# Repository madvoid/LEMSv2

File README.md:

# LEMSv2
This is the repository for the second version of the LEMS Sensor Stations. Stay tuned, information will be added as it is generated. A majority of the documentation will be added to this file. Long-term future development will happen at https://github.com/UtahEFD/LEMSv2.

### General TODO

1. Check validity of filenames with more than 8 characters
2. Decagon, the manufacturer of the 5TM soil sensors, has changed their name to Meter, and the 5TM is now called the ECH20 5TM. The DS2 is now called the Atmos 22. The documentation will need to be changed and will probably be done slowly.
3. Major Change: Change the code to read parameters from a text file on the SD card. See if possible to read code from SD card.
4. Delete or separate "File List" from README? Makes it clunky, hard to keep updated. Goal is for files to self explanatory 
5. Update DS2 code to use EnviroDIY's SDI12 library instead of custom library

### PCB TODO
1. Change the parts in the eagle files for BOM lines 11, 29, 30. These parts were out of stock and were replaced by different parts during manufacturing.

### File List
* Code/
  * `Code Instructions.md` - Instructions for uploading
  * LEMSv2/
    * `LEMSv2.ino` - LEMS Arduino Code
    * `DS3231_Alarm1.h` - Header file for corresponding `.cpp` file
    * `DS3231_Alarm1.cpp` - File used to set DS3231 Alarm 1. Developed in test code then copied to this folder
    * `d5TM.h` - Header file for corresponding `.cpp` file
    * `d5TM.cpp` - Library used to interact with 5TM. Developed in test code then copied to this folder
  * Test Code/
    * ADS1115_Test/
      * `ADS1115_Test.ino` - Test code for ADS1115 ADC
    * DS3231_Test/
      * `DS3231_Test.ino` - Test code for DS3231 RTC. Test DS3231 alarm 1
      * `DS3231_Alarm1.h` - Header file for corresponding `.cpp` file
      * `DS3231_Alarm1.c` - Library used to set DS3231 Alarm 1. Developed in here then copied to main code folder
    * DS2_Test/
      * `DS2_Test.ino` - Test code for DS2 anemometer
      * `DS2.h` - Header file for corresponding `.cpp` file
      * `DS2.cpp` - Library used to interact with DS2. Developed here then copied to main code folder
      * `LICENSE` - License to be included with the `SDI12_Zero` library
      * `LICENSE-examples.md` - License to be included with the `SDI12_Zero` library
      * `SDI12_Zero.h` - Header file for corresponding `.cpp` file
      * `SDI12_Zero.cpp` - Library used by DS2 library to interact with DS2. Implements the SDI12 protocal for Arduino Zero.
    * Li200_Test/
      * `Li200_Test.ino` - Test Li200 with intermediate values in calculations printed
    * Teros21_Test/
      * `Teros21_Test.ino` - Test Teros21 and library.
    * Test_5TM/
      * `Test_5TM.ino` - Test code for 5TM Library. 5TM has been working since LEMSv1 but is now made into a library.
      * `d5TM.h` - Header file for corresponding `.cpp` file
      * `d5TM.cpp` - Library used to interact with 5TM. Developed here then copied to main code folder
  * Time_Set/
    * `Time_Set.ino` - Code used to set the time on the DS3231 real time clock
* Data Manipulation/
  * `LemsPlot.m` - View LEMSv2 data plots. Not perfectly adaptable to any file, but will work for a fully instrumented station. To work properly, requires the [Intelligent Dynamic Date Ticks](https://www.mathworks.com/matlabcentral/fileexchange/27075-intelligent-dynamic-date-ticks) file from MathWorks. Can work without it though by commenting out the lines that use it.
  * `importfile.m` - Used to import the LEMSv2 data files. Can only be used on data files from fully instrumented LEMS.
* Hardware Information/
  * `Bill of Materials.xlsx` - Complete parts list
  * `Calibration Constants.xlsx` - Calibration constants for various instruments. For now, only contains Li200 constants.
  * Data Sheets/
    * Multiple data sheets for components
  * Li200R Base/
    * Solidworks/
      * Contains Solidworks files for Li200R base
    * STL Files/
      * Contains print ready STL files for Li200R base
    * `Build Instructions.md` - Tools required for making the Li200R base
  * MLX Housing/
    * `MLX Housing Build Instructions` - Build instructions for MLX90615 housing
  * PCB/
    * `LEMSv2 Board.pdf` - PDF of PCB for easy reference
    * `LEMSv2 Schematic.pdf` - PDF of schematic for easy reference
    * `SAMD21 Breakout Board.jpg` - Reference picture for microcontroller board
  * `Pin List.xlsx` - Pin connection list for SAMD21 Dev Breakout Board
  * `Possible Parts.txt` - Potential parts/Manufacturers to add/use in the future
  * Transimpedance Amplifier/
    * `Transimpedance_Amplifier_Calculations.ipynb` - Jupyter notebook containing transimpedance amplifier calculations
  * `Wiring Information.xlsx` - Information about wiring. What connects to what, etc. Work in progress.
* `LICENSE.TXT` - License
* PCB/
  * LEMSv2 PCB/
    * `Centroid_ScreamingCircuits_smd.ulp` - Eagle ULP script to create centroid data for screaming circuits
    * Gerbers/
      * Contains gerbers for board, plus the panelized gerbers supplied by OSH Park. Also contains the centroid file for Screaming Circuits.
    * `LEMSv2.sch` - LEMSv2 shield schematic
    * `LEMSv2.brd` - LEMSv2 shield layout
    * `OSH_DesignRules.dru` - Eagle design rules for OSH Park
    * `OSHPark_2layer_Eagle7.2.cam` - Modified cam job for OSH Park
  * LEMSv2 PCB Library/
    * `LEMSv2.lbr` - Parts used in the LEMSv2 shield
* `Possible Problems.md` - List of potential hardware problems in the LEMS. Prefer to not have duplicate entries, i.e. one line per problem.
* `README.md` - If you read this line you're actually reading the README. Good job!

### Dependencies
Only 3rd party software dependencies are included in this list. Libraries built into the Arduino software or created for the LEMSv2 software isn't included. You will need the most recent version of the [Arduino IDE](https://www.arduino.cc/en/Main/Software) installed.

* [Adafruit RTC Library](https://github.com/adafruit/RTClib)
* [Adafruit SHT31 Library](https://github.com/adafruit/Adafruit_SHT31)
* [Adafruit Sensor Library](https://github.com/adafruit/Adafruit_Sensor)
* [Adafruit BMP280 Library](https://github.com/adafruit/Adafruit_BMP280_Library)
* [Adafruit MLX90614 Library](https://github.com/adafruit/Adafruit-MLX90614-Library)
* [EnviroDIY SDI-12 Library](https://github.com/EnviroDIY/Arduino-SDI-12) 
* [Soligen2010's fork of the Adafruit ADS1x15 Library](https://github.com/soligen2010/Adafruit_ADS1X15). The default Adafruit ADS1x15 library **doesn't** work.
* In addition, the Sparkfun SAMD21 [board definition](https://raw.githubusercontent.com/sparkfun/Arduino_Boards/master/IDE_Board_Manager/package_sparkfun_index.json
  ) needs to be installed into the Arduino IDE. See [here](https://learn.sparkfun.com/tutorials/samd21-minidev-breakout-hookup-guide/setting-up-arduino) for more info.

### Miscellaneous Notes

- ADS1115 single ended resolution calculation information can be found [here](https://e2e.ti.com/support/data_converters/precision_data_converters/f/73/t/489070)
- ADS1115 over range input information can be found [here](https://e2e.ti.com/support/data_converters/precision_data_converters/f/73/p/398187/1407689#1407689) and [here](https://e2e.ti.com/support/data_converters/precision_data_converters/f/73/t/378122)

### Acknowledgements

* Thanks to [Sparkfun](https://www.sparkfun.com) and [Adafruit](https://www.adafruit.com) for Arduino libraries, components, tutorials, and eagle parts. Many designs and eagle components are directly used from them. Also thanks to [OSH Park](www.oshpark.com) and [Screaming Circuits](www.screamingcircuits.com) for the excellent PCBs and assembly. They were instrumental in getting LEMSv2 completed.

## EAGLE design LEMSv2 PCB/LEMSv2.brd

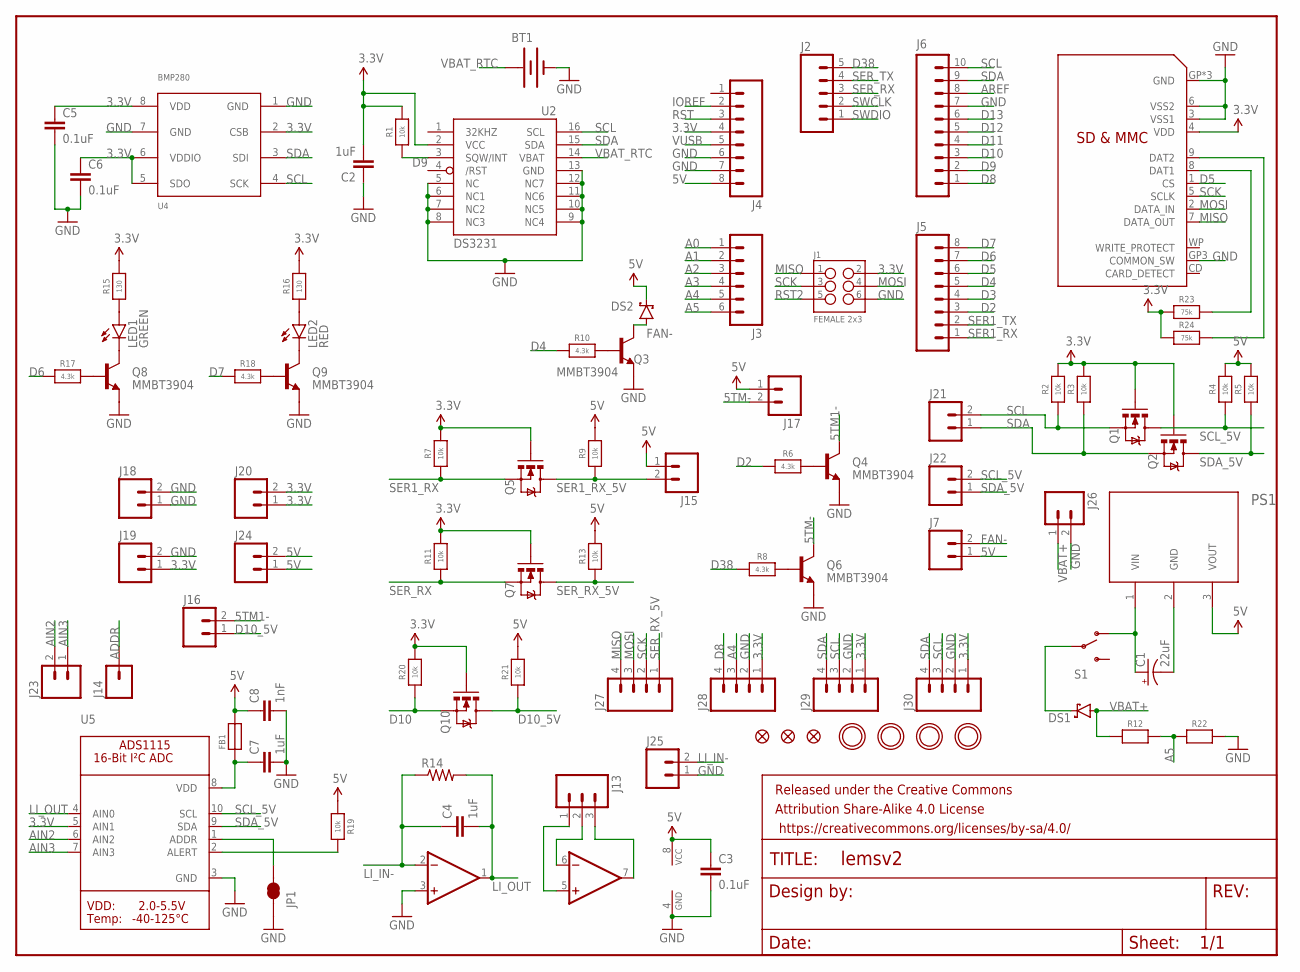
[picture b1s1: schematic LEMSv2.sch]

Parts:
BT1: BATTERY12MM; BATTCON_12MM
C1: 22uF; CPOL-RADIAL-10UF-25V
C2, C4, C7: 1uF; _0805
C3, C5, C6: 0.1uF; _0805
C8: 1nF; _0805
DS1, DS2: DIODE_SCHOTTKY; DO-214AC
FB1: FERRITE; _0805
FID1, FID2, FID3: FIDUCIAL""; FIDUCIAL_1MM
FRAME1: FRAME-LETTERNO_PACKAGE; DUMMY
J1: FEMALE 2x3; 2X3
J2: M05PTH; 1X05
J3: M06SILK_FEMALE_PTH; 1X06
J4, J5: M08; 1X08_ROUND
J6: M10SILK_FEMALE_PTH; 1X10
J7, J15, J16, J17, J18, J19, J20, J21, J22, J23, J24, J25, J26: M023.5MM; SCREWTERMINAL-3.5MM-2
J13: M03PTH; 1X03
J14: M01PTH; 1X01
J27, J28, J29, J30: M04SCREW; SCREWTERMINAL-3.5MM-4
JP1: JUMPER-PAD-2-NC_BY_TRACE; PAD-JUMPER-2-NC_BY_TRACE_YES_SILK
LED1: GREEN; LED-0603
LED2: RED; LED-0603
PS1: TSR_1-2450
Q1, Q2, Q5, Q7, Q10: 200mA/50V; SOT23-3
Q3, Q4, Q6, Q8, Q9: MMBT3904; SOT23-3
R1, R2, R3, R4, R5, R7, R9, R11, R13, R19, R20, R21: 10k; _0805
R6, R8, R10, R17, R18: 4.3k; _0805
R12, R22: RESISTOR_0805; _0805
R14: R-US_FLIPFLOP; 0805-THM
R15, R16: 130; _0805
R23, R24: 75k; _0805
S1: SWITCH-SPDTPTH; SWITCH-SPDT
U1: SDMMC06132; 06132
U2: DS3231/SO; SO16W
U3: TLV2372; SOIC8
U4: BMP280
U5: ADC_ADS1115; MSOP10
U$1, U$2, U$3, U$4: MOUNTINGHOLE2.5; MOUNTINGHOLE_2.5_PLATED

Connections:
3.3V: C2.2, C5.1, C6.1, J1.2, J4.4, J19.1, J20.1, J20.2, J28.1, J29.1, J30.1, Q1.1 (G), Q2.1 (G), Q5.1 (G), Q7.1 (G), Q10.1 (G), R1.2, R2.2, R3.2, R7.2, R11.2, R15.2, R16.2, R20.2, R23.1, R24.1, U1.4 (VDD), U2.2 (VCC), U4.2 (CSB), U4.5 (SDO), U4.6 (VDDIO), U4.8 (VDD), U5.5 (AIN1)
5TM1-: J16.2, Q4.3 (C)
5TM-: J17.2, Q6.3 (C)
5V: C3.1, C8.1, DS2.C, FB1.2, J4.8, J7.1, J15.1, J17.1, J24.1, J24.2, PS1.3 (VOUT), R4.2, R5.2, R9.2, R13.2, R19.1, R21.2, U3.8 (VCC)
A0: J3.1
A1: J3.2
A2: J3.3
A3: J3.4
A4: J3.5, J28.3
A5: J3.6, R12.2, R22.1
ADDR: J14.1, JP1.1, U5.1 (ADDR)
AIN2: J23.2, U5.6 (AIN2)
AIN3: J23.1, U5.7 (AIN3)
ALERT: R19.2, U5.2 (ALERT)
AREF: J6.8
D2: J5.3, R6.1
D3: J5.4
D4: J5.5, R10.1
D5: J5.6, U1.1 (CS)
D6: J5.7, R17.1
D7: J5.8, R18.1
D8: J6.1, J28.4
D9: J6.2, R1.1, U2.3 (SQW/INT)
D10: J6.3, Q10.2 (S), R20.1
D10_5V: J16.1, Q10.3 (D), R21.1
D11: J6.4
D12: J6.5
D13: J6.6
D38: J2.5, R8.1
FAN-: DS2.A, J7.2, Q3.3 (C)
GND: BT1.GND (-), C1.2 (-), C2.1, C3.2, C5.2, C6.2, C7.2, C8.2, J1.6, J4.6, J4.7, J6.7, J18.1, J18.2, J19.2, J25.1, J26.2, J28.2, J29.2, J30.2, JP1.2, PS1.2 (GND), Q3.2 (E), Q4.2 (E), Q6.2 (E), Q8.2 (E), Q9.2 (E), R22.2, U1.3 (VSS1), U1.6 (VSS2), U1.GP (GND), U1.GP2 (GND), U1.GP3 (COMMON_SW), U1.GP4 (GND), U2.5 (NC), U2.6 (NC1), U2.7 (NC2), U2.8 (NC3), U2.9 (NC4), U2.10 (NC5), U2.11 (NC6), U2.12 (NC7), U2.13 (GND), U3.3 (+IN), U3.4 (GND), U4.1 (GND), U4.7 (GND), U5.3 (GND)
IOREF: J4.2
LI_IN-: C4.1, J25.2, R14.1, U3.2 (-IN)
LI_OUT: C4.2, R14.2, U3.1 (OUT), U5.4 (AIN0)
MISO: J1.1, J27.4, U1.7 (DATA_OUT)
MOSI: J1.4, J27.3, U1.2 (DATA_IN)
unnamed: C1.1 (+), PS1.1 (VIN), S1.1 (O)
unnamed: J13.2, U3.6 (-IN)
unnamed: J13.1, U3.5 (+IN)
unnamed: J13.3, U3.7 (OUT)
unnamed: Q8.1 (B), R17.2
unnamed: Q9.1 (B), R18.2
unnamed: LED1.C, Q8.3 (C)
unnamed: LED2.C, Q9.3 (C)
unnamed: LED1.A, R15.1
unnamed: LED2.A, R16.1
unnamed: Q4.1 (B), R6.2
unnamed: Q6.1 (B), R8.2
unnamed: DS1.C, S1.2
unnamed: C7.1, FB1.1, U5.8 (VDD)
unnamed: Q3.1 (B), R10.2
unnamed: R23.2, U1.8 (DAT1)
unnamed: R24.2, U1.9 (DAT2)
RST: J4.3
RST2: J1.5
SCK: J1.3, J27.2, U1.5 (SCLK)
SCL: J6.10, J21.2, J29.3, J30.3, Q1.2 (S), R2.1, U2.16 (SCL), U4.4 (SCK)
SCL_5V: J22.2, Q1.3 (D), R4.1, U5.10 (SCL)
SDA: J6.9, J21.1, J29.4, J30.4, Q2.2 (S), R3.1, U2.15 (SDA), U4.3 (SDI)
SDA_5V: J22.1, Q2.3 (D), R5.1, U5.9 (SDA)
SER1_RX: J5.1, Q5.2 (S), R7.1
SER1_RX_5V: J15.2, Q5.3 (D), R9.1
SER1_TX: J5.2
SER_RX: J2.3, Q7.2 (S), R11.1
SER_RX_5V: J27.1, Q7.3 (D), R13.1
SER_TX: J2.4
SWCLK: J2.2
SWDIO: J2.1
VBAT+: DS1.A, J26.1, R12.1
VBAT_RTC: BT1.PWR@1 (+), U2.14 (VBAT)
VUSB: J4.5

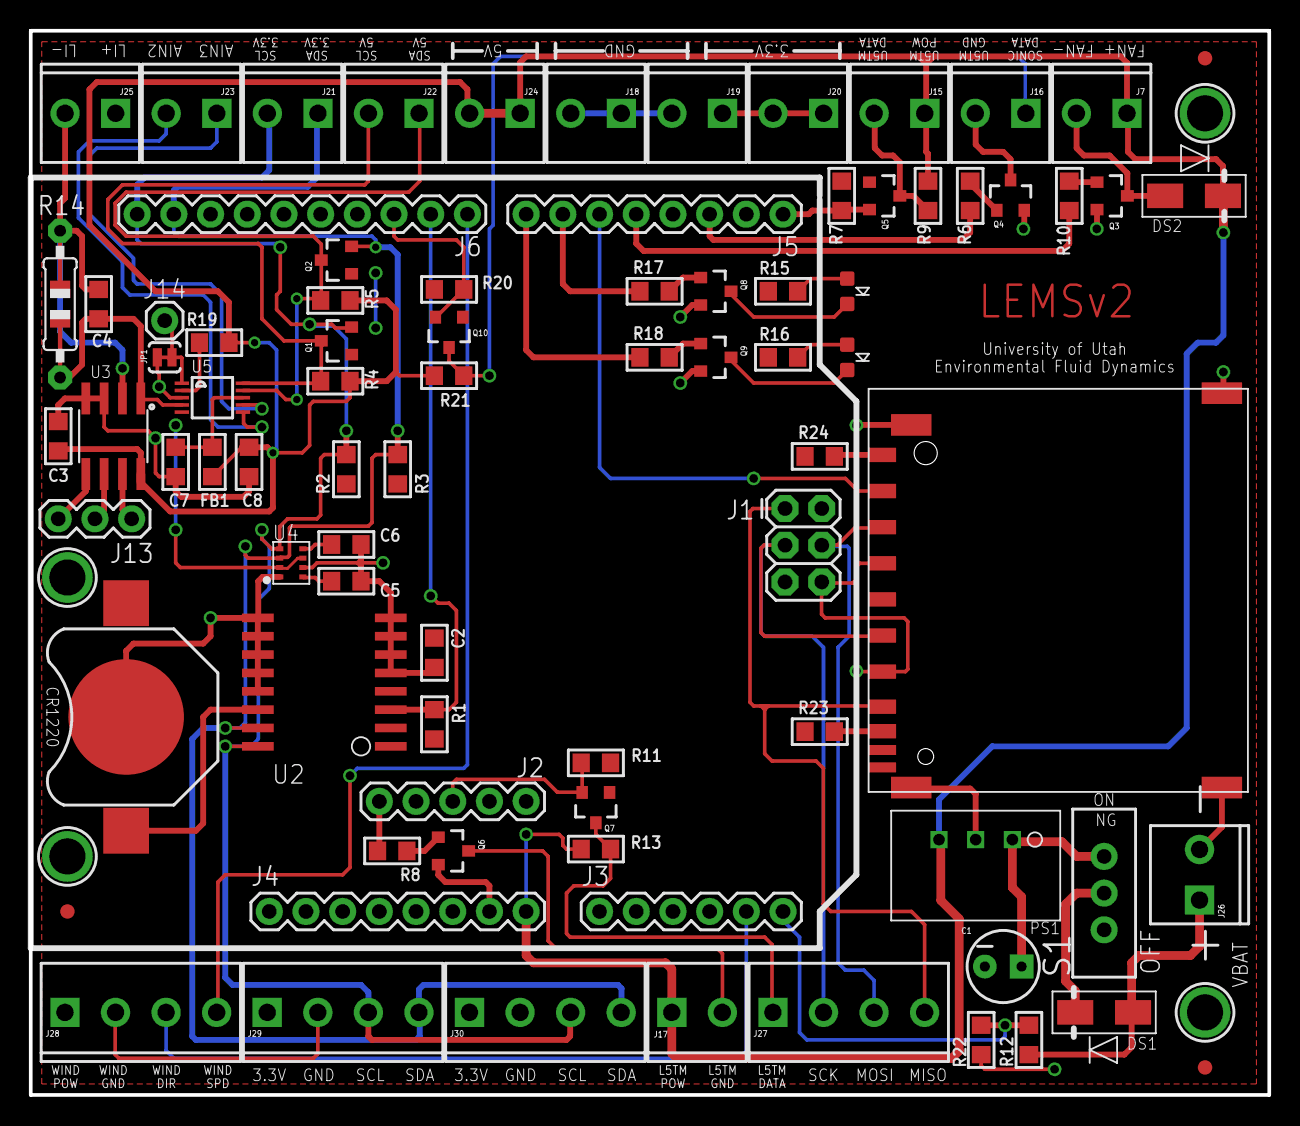
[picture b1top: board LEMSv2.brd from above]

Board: 2 copper layers, 85.7 x 73.7 mm, 89 parts (0 on the bottom side), 54 nets.

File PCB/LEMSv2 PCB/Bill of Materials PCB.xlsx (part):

TH = Through Hole |  | SMT = Surface Mount | Shipping costs not included! | Octopart has alt. distributors
Information |  |  |  |  |  | Price/Unit |  | Price/10 Units |  | Price/25 Units |  | Ordering |  |  |  | Notes
Place | Reference Designator | Manufacturer | Manufacturer Part Number | Part Description | Quantity/Board | Cost/Part | Total Quantity Cost | Cost/Part | Total Quantity Cost | Cost/Part | Total Quantity Cost | Source | Distributor Part Number | Package | Distributor Link
Yes | J7, J15-J26 | On Shore Technology Inc. | OSTTE020104 | 2-Pin 3.5mm Screw Terminal | 13 | 0.38 | 4.9400000000000004 | 0.36399999999999999 | 47.32 | 0.312 | 101.4 | Digikey | ED2740-ND | 3.5mm Spacing TH | http://www.digikey.com/product-detail/en/on-shore-technology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
Yes | J27-J30 | On Shore Technology Inc. | OSTTE040104 | 3-Pin 3.5mm Screw Terminal | 4 | 0.67 | 2.68 | 0.624 | 24.96 | 0.56159999999999999 | 56.16 | Digikey | ED2742-ND | 3.5mm Spacing TH | http://www.digikey.com/product-detail/en/on-shore-technology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
Yes | PS1 | Traco Power | TSR 1-2450 | DC/DC 5V Regulator | 1 | 6.2 | 6.2 | 5.7 | 57 | 5.43 | 135.75 | Mouser | 495-TSR-1-2450 | SIP-3 | http://www.mouser.com/ProductDetail/TRACO-Power/TSR-1-2450/?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
No | C1 | Panasonic Electronics | ECA-1HM220 | 22uF 50V Capacitor | 1 | 0.22 | 0.22 | 0.153 | 1.53 | 0.1124 | 2.81 | Digikey | P5179-ND | 5mm Diam. Radial TH | http://www.digikey.com/product-detail/en/ECA-1HM220/P5179-ND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
Yes | U1 | TE Connectivity | 2041021-3 | SD Card Holder | 1 | 1.74 | 1.74 | 1.74 | 17.399999999999999 | 1.49 | 37.25 | Newark | 35R2925 | N/A | http://www.newark.com/te-connectivity/2041021-3/memory-card-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
Yes | U2 | Maxim Integrated | DS3231SN#T&R | DS3231 Real Time Clock | 1 | 9.9700000000000006 | 9.9700000000000006 | 9.41 | 94.1 | 7.5275999999999996 | 188.19 | Digikey | DS3231SN#T&RCT-ND | SOIC-16 | http://www.digikey.com/product-detail/en/DS3231SN%2523T%26R/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
Yes | R1-R5, R7, R9, R11, R13, R19-R21 | Yageo | RC0805FR-0710KL | 10k 1% 1/8W Resistor | 12 | 0.1 | 1.2000000000000002 | 2.1000000000000001E-2 | 2.52 | 1.52E-2 | 4.5600000000000005 | Digikey | 311-10.0KCRCT-ND | 0805 (Imperial) | http://www.digikey.com/product-detail/en/RC0805FR-0710KL/311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
Yes | C2, C4, C7 | Taiyo Yuden | UMK212B7105KG-T | 1uF 50V Ceramic Capacitor | 3 | 0.21 | 0.63 | 0.14099999999999999 | 4.2299999999999995 | 0.14099999999999999 | 10.574999999999998 | Digikey | 587-2910-1-ND | 0805 (Imperial) | https://www.digikey.com/product-detail/en/taiyo-yuden/UMK212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
Yes | BT1 | Keystone Electronics | 3000 | 12mm Battery Holder | 1 | 0.57999999999999996 | 0.57999999999999996 | 0.54500000000000004 | 5.45 | 0.54500000000000004 | 13.625000000000002 | Digikey | 36-3000-ND | SMT | http://www.digikey.com/product-detail/en/3000/36-3000-ND/227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
Yes | LED1 | Lite-On Inc. | LTST-C190GKT | Green LED | 1 | 0.27 | 0.27 | 0.19600000000000001 | 1.96 | 0.14480000000000001 | 3.62 | Digikey | 160-1183-1-ND | 0603 (Imperial) | http://www.digikey.com/product-detail/en/LTST-C190GKT/160-11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
Yes | LED2 | Lite-On Inc. | LTST-C190KRKT | Red LED | 1 | 0.27 | 0.27 | 0.19600000000000001 | 1.96 | 0.14480000000000001 | 3.62 | Digikey | 160-1436-1-ND | 0603 (Imperial) | http://www.digikey.com/product-detail/en/LTST-C190KRKT/160-1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
Yes | R6, R8, R10, R17, R18 | Yageo | RC0805FR-074K3L | 4.3k 1% 1/8W Resistor | 5 | 0.1 | 0.5 | 2.1000000000000001E-2 | 1.05 | 1.52E-2 | 1.9 | Digikey | 311-4.30KCRCT-ND | 0805 (Imperial) | http://www.digikey.com/product-detail/en/RC0805FR-074K3L/311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
Yes | R15, R16 | Yageo | RC0805FR-07130RL | 130 Ohm 1% 1/8W Resistor | 2 | 0.1 | 0.2 | 2.1000000000000001E-2 | 0.42000000000000004 | 1.52E-2 | 0.76 | Digikey | 311-130CRCT-ND | 0805 (Imperial) | http://www.digikey.com/product-detail/en/RC0805FR-07130RL/31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
Yes | Q3, Q4, Q6, Q8, Q9 | Micro Commercial Co | MMBT3904-TP | NPN Transistor | 5 | 0.1 | 0.5 | 8.5999999999999993E-2 | 4.2999999999999989 | 7.8399999999999997E-2 | 9.8000000000000007 | Digikey | MMBT3904TPMSCT-ND | SOT-23 | https://www.digikey.com/products/en?keywords=MMBT3904TPMSCT-ND
Yes | FB1 | TDK Corp. | MMZ2012Y152BT000 | 1.5kOhm Imp. 400 mOhm Ferrite Bead | 1 | 0.11 | 0.11 | 8.7999999999999995E-2 | 0.87999999999999989 | 8.7999999999999995E-2 | 2.1999999999999997 | Digikey | 445-1560-1-ND | 0805 (Imperial) | http://www.digikey.com/product-detail/en/MMZ2012Y152BT000/44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
Yes | C8 | Murata | GRM2165C1H102JA01D | 1000pF 50V Ceramic Capacitor | 1 | 0.12 | 0.12 | 8.7999999999999995E-2 | 0.87999999999999989 | 8.7999999999999995E-2 | 2.1999999999999997 | Digikey | 490-1622-1-ND | 0805 (Imperial) | https://www.digikey.com/products/en?keywords=490-1622-1-ND
Yes | U5 | Texas Instruments | ADS1115IDGSR | 16-bit 4-Channel ADC | 1 | 5.65 | 5.65 | 5.0720000000000001 | 50.72 | 5.0720000000000001 | 126.8 | Digikey | 296-38849-1-ND | 10-MSOP | http://www.digikey.com/product-detail/en/ADS1115IDGSR/296-38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
Yes | S1 | E-Switch | EG1218 | SPDT Switch | 1 | 0.56000000000000005 | 0.56000000000000005 | 0.54200000000000004 | 5.42 | 0.53100000000000003 | 13.275 | Mouser | 612-EG1218 | 2.5mm TH | http://www.mouser.com/ProductDetail/E-Switch/EG1218/?qs=sGAE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
Yes | J1 | Sullins Connector | PPPC032LFBN-RC | 2x3 TH Female Header | 1 | 0.82 | 0.82 | 0.64 | 6.4 | 0.5968 | 14.92 | Digikey | S7106-ND | 0.1" TH | http://www.digikey.com/product-detail/en/sullins-connector-s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 | TH is used instead of SMT because the SMT parts are considered through hole by 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
Yes | J2 | Sullins Connector | PPPC051LFBN-RC | 1x5 TH Female Header | 1 | 0.65 | 0.65 | 0.502 | 5.0199999999999996 | 0.46760000000000002 | 11.690000000000001 | Digikey | S7038-ND | 0.1" TH | http://www.digikey.com/product-detail/en/sullins-connector-s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 | TH is used instead of SMT because the SMT parts are considered through hole by 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
Yes | J3 | Sullins Connector | PPPC061LFBN-RC | 1x6 TH Female Header | 1 | 0.7 | 0.7 | 0.54600000000000004 | 5.4600000000000009 | 0.50880000000000003 | 12.72 | Digikey | S7039-ND | 0.1" TH | http://www.digikey.com/product-detail/en/sullins-connector-s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 | TH is used instead of SMT because the SMT parts are considered through hole by 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
Yes | J4, J5 | Sullins Connector | PPPC081LFBN-RC | 1x8 TH Female Header | 2 | 0.89 | 1.78 | 0.69 | 13.799999999999999 | 0.64359999999999995 | 32.18 | Digikey | S7041-ND | 0.1" TH | http://www.digikey.com/product-detail/en/sullins-connector-s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 | TH is used instead of SMT because the SMT parts are considered through hole by 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
Yes | J6 | Sullins Connector | PPPC101LFBN-RC | 1x10 TH Female Header | 1 | 0.84 | 0.84 | 0.69899999999999995 | 6.9899999999999993 | 0.64759999999999995 | 16.189999999999998 | Digikey | S7043-ND | 0.1" TH | http://www.digikey.com/product-detail/en/sullins-connector-s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 | TH is used instead of SMT because the SMT parts are considered through hole by 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
No | J14 |  |  | 1x1 TH Female Header | 1 |  | 0 |  | 0 |  | 0 |  |  | 0.1" TH |  | Future Expansion Connector
No | J13 |  |  | 1x3 TH Female Header | 1 |  | 0 |  | 0 |  | 0 |  |  | 0.1" TH |  | Future Expansion Connector
Yes | Q1, Q2, Q5, Q7, Q10 | ON Semiconductor | BSS138 | N-Channel MOSFET | 5 | 0.27 | 1.35 | 0.17799999999999999 | 8.8999999999999986 | 0.17799999999999999 | 22.249999999999996 | Mouser | 512-BSS138 | SOT-23 | https://www.mouser.com/ProductDetail/ON-Semiconductor-Fairch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
Yes | C3, C5, C6 | Avx Corp. | 08055F104K4T2A | 0.1uF 50V Ceramic Capacitor | 3 | 0.38 | 1.1400000000000001 | 0.26600000000000001 | 7.98 | 0.26600000000000001 | 19.950000000000003 | Digikey | 478-3614-1-ND | 0805 (Imperial) | https://www.digikey.com/products/en?keywords=478-3614-1-ND
Yes | U3 | Texas Instruments | TLV2372IDR | 2-Channel Rail-To-Rail Op-Amp | 1 | 1.61 | 1.61 | 1.37 | 13.700000000000001 | 1.37 | 34.25 | Mouser | 595-TLV2372IDR | SOIC-8 | http://www.mouser.com/ProductDetail/Texas-Instruments/TLV237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
No | R14 |  |  | Gain Resistor | 1 |  | 0 |  | 0 |  | 0 |  |  |  |  | Not added yet
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
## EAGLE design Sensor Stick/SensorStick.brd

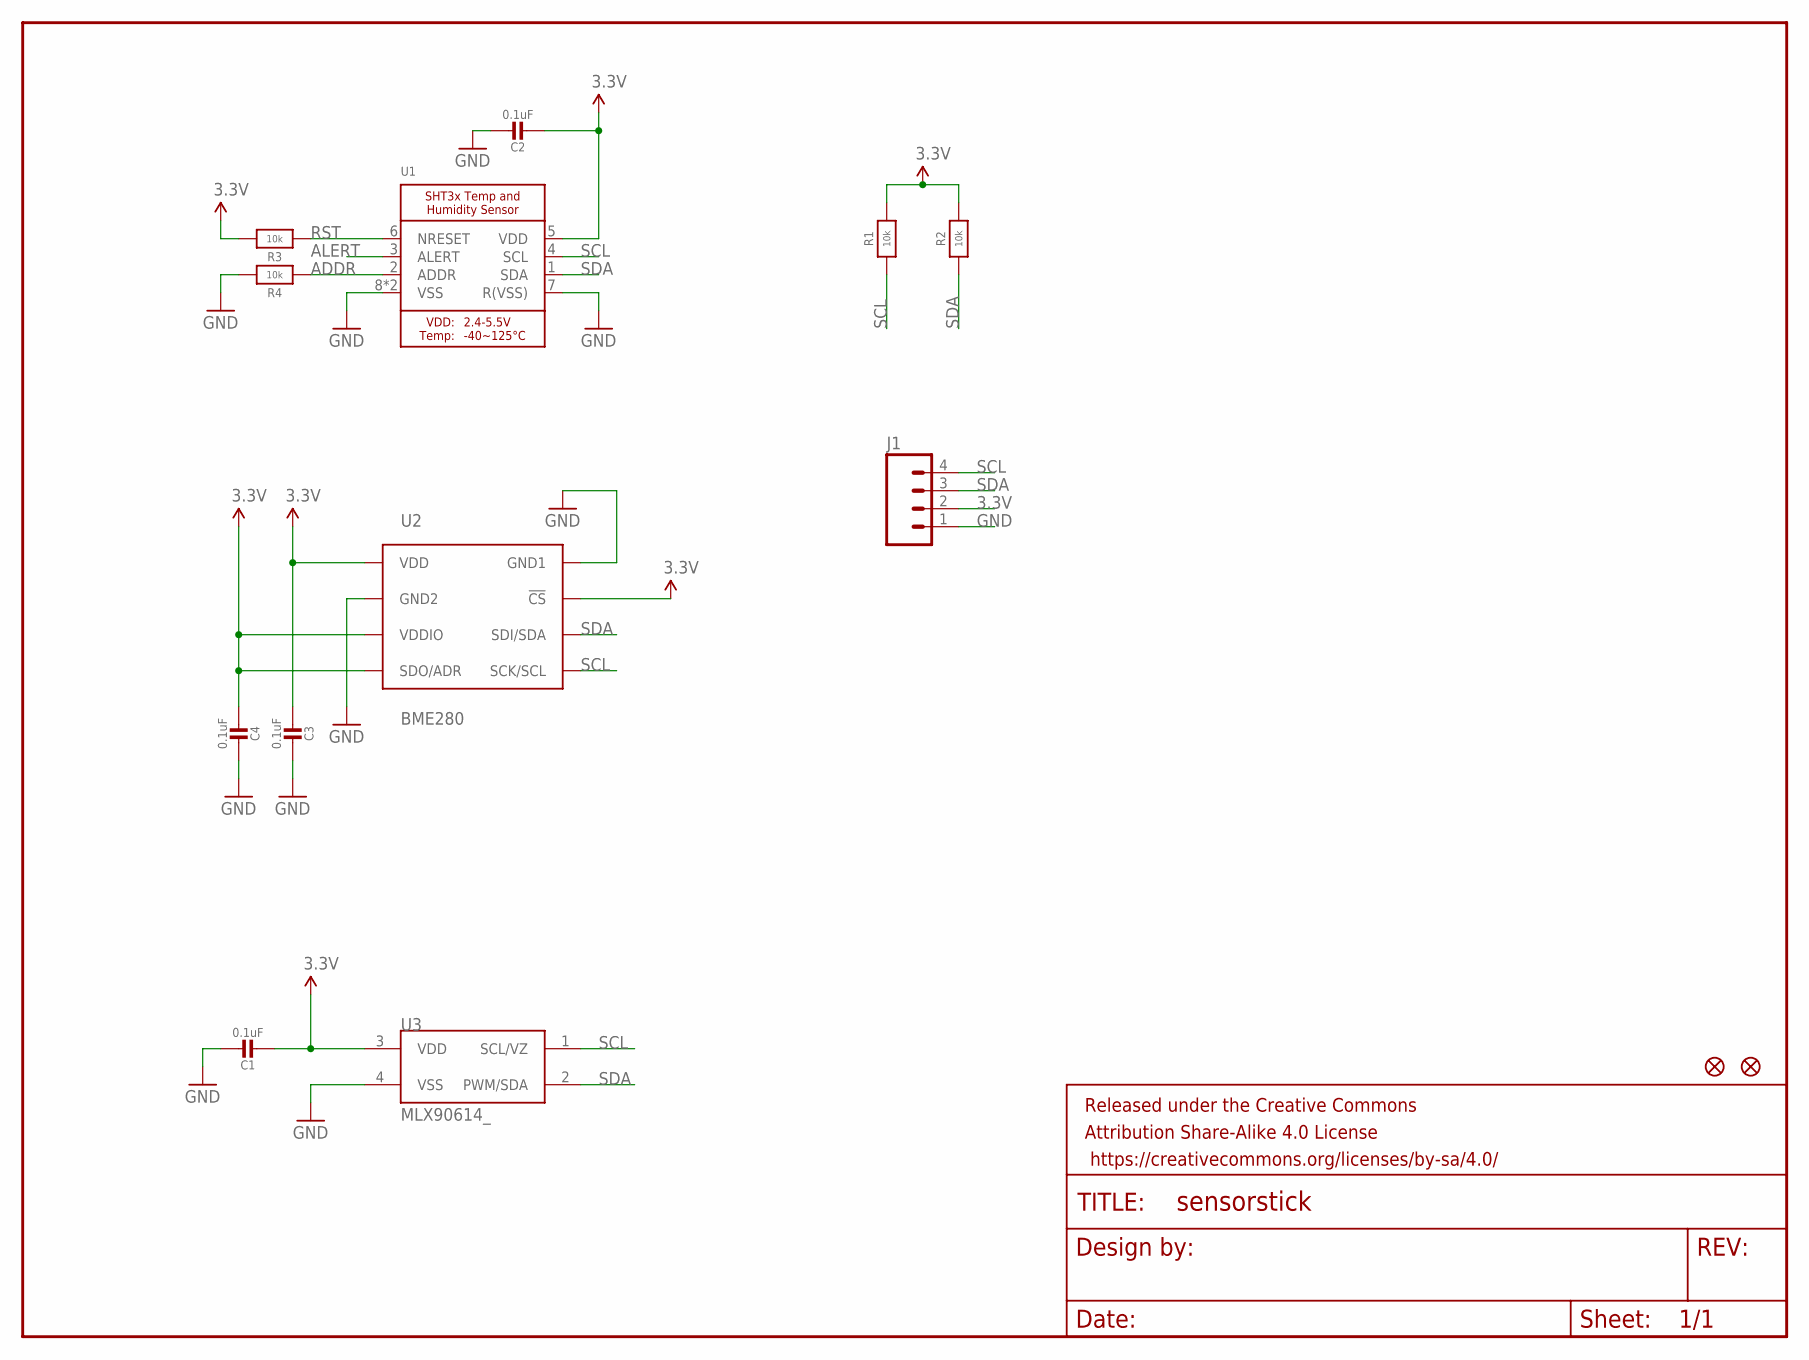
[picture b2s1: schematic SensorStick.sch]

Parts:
C1, C2, C3, C4: 0.1uF; _0805
FID1, FID2: SPARKFUN-AESTHETICS_FIDUCIAL1X2; SPARKFUN-AESTHETICS_FIDUCIAL-1X2
FRAME1: FRAME-LETTERNO_PACKAGE; DUMMY
J1: M04PTH; 1X04
R1, R2, R3, R4: 10k; _0805
U1: SHT3X
U2: BME280; BME280COMPONENTLIBRARY_BME280_LGA
U3: MLX90614_; TO-39

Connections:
3.3V: C1.2, C2.2, C3.2, C4.2, J1.2, R1.2, R2.2, R3.2, U1.5 (VDD), U2.P$2 (!CS), U2.P$5 (SDO/ADR), U2.P$6 (VDDIO), U2.P$8 (VDD), U3.3 (VDD)
ADDR: R4.1, U1.2 (ADDR)
ALERT: U1.3 (ALERT)
GND: C1.1, C2.1, C3.1, C4.1, J1.1, R4.2, U1.7 (R(VSS)), U1.8 (VSS), U1.THERMAL (VSS), U2.P$1 (GND1), U2.P$7 (GND2), U3.4 (VSS)
RST: R3.1, U1.6 (NRESET)
SCL: J1.4, R1.1, U1.4 (SCL), U2.P$4 (SCK/SCL), U3.1 (SCL/VZ)
SDA: J1.3, R2.1, U1.1 (SDA), U2.P$3 (SDI/SDA), U3.2 (PWM/SDA)

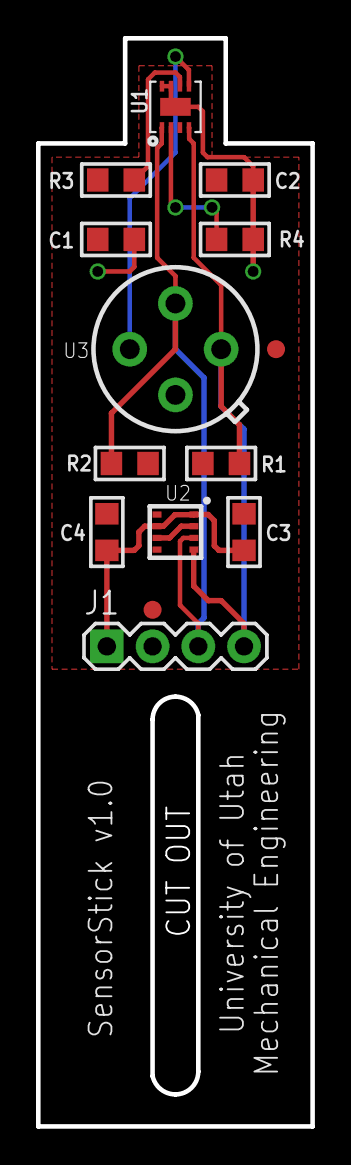
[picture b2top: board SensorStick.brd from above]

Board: 2 copper layers, 15.2 x 60.5 mm, 15 parts (0 on the bottom side), 6 nets.

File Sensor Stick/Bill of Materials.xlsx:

Number of Prototypes: |  |  | 1 | Shipping costs not included!
Information |  |  |  |  | Ideal Cost/Unit |  | Ideal Cost/10 Units |  | Ideal Cost/25 Units |  | Ordering |  |  |  | Notes
Schematic Name | Manufacturer | Manufacturer Part Number | Part | Quantity/Board | Cost/Unit | Prototype Cost | Cost/Unit | Prototype Cost | Cost/Unit | Prototype Cost | Distributor | Distributor Part Number | Package | Link
U3 | Melexis | MLX90614ESF-BAA-000-TU | Infrared Thermometer | 1 | 14.08 | 14.08 | 12.79 | 127.89999999999999 | 11.83 | 295.75 | Mouser | 482-90614ESFBAA000TU | TO-39-4 | http://www.mouser.com/ProductDetail/Melexis/MLX90614ESF-BAA-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
U2 | Bosch | BME280 | Temp/Pressure/Humidity Sensor | 1 | 5.66 | 5.66 | 5.66 | 56.6 | 5.66 | 141.5 | Mouser | 262-BME280 | LGA-8 | http://www.mouser.com/ProductDetail/Bosch/BME280/?qs=%2fha2p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
U1 | Sensirion | SHT31-DIS-B | Temp/Humidity Sensor | 1 | 6.91 | 6.91 | 5.35 | 53.5 | 5.35 | 133.75 | Mouser | 403-SHT31-DIS-B | DFN-8 | http://www.mouser.com/ProductDetail/Sensirion/SHT31-DIS-B/?q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
C1,C2,C3,C4 | Murata | GRM21BR71H104KA01L | 0.1uF Capacitor | 4 | 0.17 | 0.68 | 7.1999999999999995E-2 | 2.88 | 7.1999999999999995E-2 | 7.1999999999999993 | Mouser | 81-GRM40X104K50L | 0805 | http://www.mouser.com/ProductDetail/Murata/GRM21BR71H104KA01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
R1,R2,R3,R4 | Yageo | RC0805FR-0710KL | 10k Resistor | 4 | 0.1 | 0.4 | 1.6E-2 | 0.64 | 1.6E-2 | 1.6 | Mouser | 603-RC0805FR-0710KL | 0805 | http://www.mouser.com/ProductDetail/Yageo/RC0805FR-0710KL/?q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
 |  |  |  |  |  | 0 |  | 0 |  | 0
 |  |  |  |  |  | 0 |  | 0 |  | 0
 |  |  |  |  |  | 0 |  | 0 |  | 0
 |  |  |  |  |  | 0 |  | 0 |  | 0
 |  |  |  |  |  | 0 |  | 0 |  | 0
 |  |  |  |  |  | 0 |  | 0 |  | 0
 |  |  |  |  |  | 0 |  | 0 |  | 0
 |  |  |  |  |  | 0 |  | 0 |  | 0
 |  |  |  |  |  | 0 |  | 0 |  | 0
 |  |  |  |  |  | 0 |  | 0 |  | 0
 |  |  |  |  |  | 0 |  | 0 |  | 0
 |  |  |  |  |  | 0 |  | 0 |  | 0
 |  |  |  |  |  | 0 |  | 0 |  | 0
 |  |  |  |  |  | 0 |  | 0 |  | 0
 |  |  |  |  |  | 0 |  | 0 |  | 0
 |  |  |  |  |  | 0 |  | 0 |  | 0
 |  |  |  |  |  | 0 |  | 0 |  | 0
 |  |  |  |  |  | 0 |  | 0 |  | 0
 |  |  |  |  |  | 0 |  | 0 |  | 0
 |  |  |  |  |  | 0 |  | 0 |  | 0
 |  |  |  |  |  | 0 |  | 0 |  | 0
 |  |  |  |  |  | 0 |  | 0 |  | 0
 |  |  |  |  | Total Prototype Cost: | 27.73 | Total Prototype Cost: | 241.51999999999998 | Total Prototype Cost: | 579.80000000000007
 |  |  |  |  | Prototype Cost/Unit: | 27.73 | Prototype Cost/Unit: | 24.151999999999997 | Prototype Cost/Unit: | 23.192000000000004

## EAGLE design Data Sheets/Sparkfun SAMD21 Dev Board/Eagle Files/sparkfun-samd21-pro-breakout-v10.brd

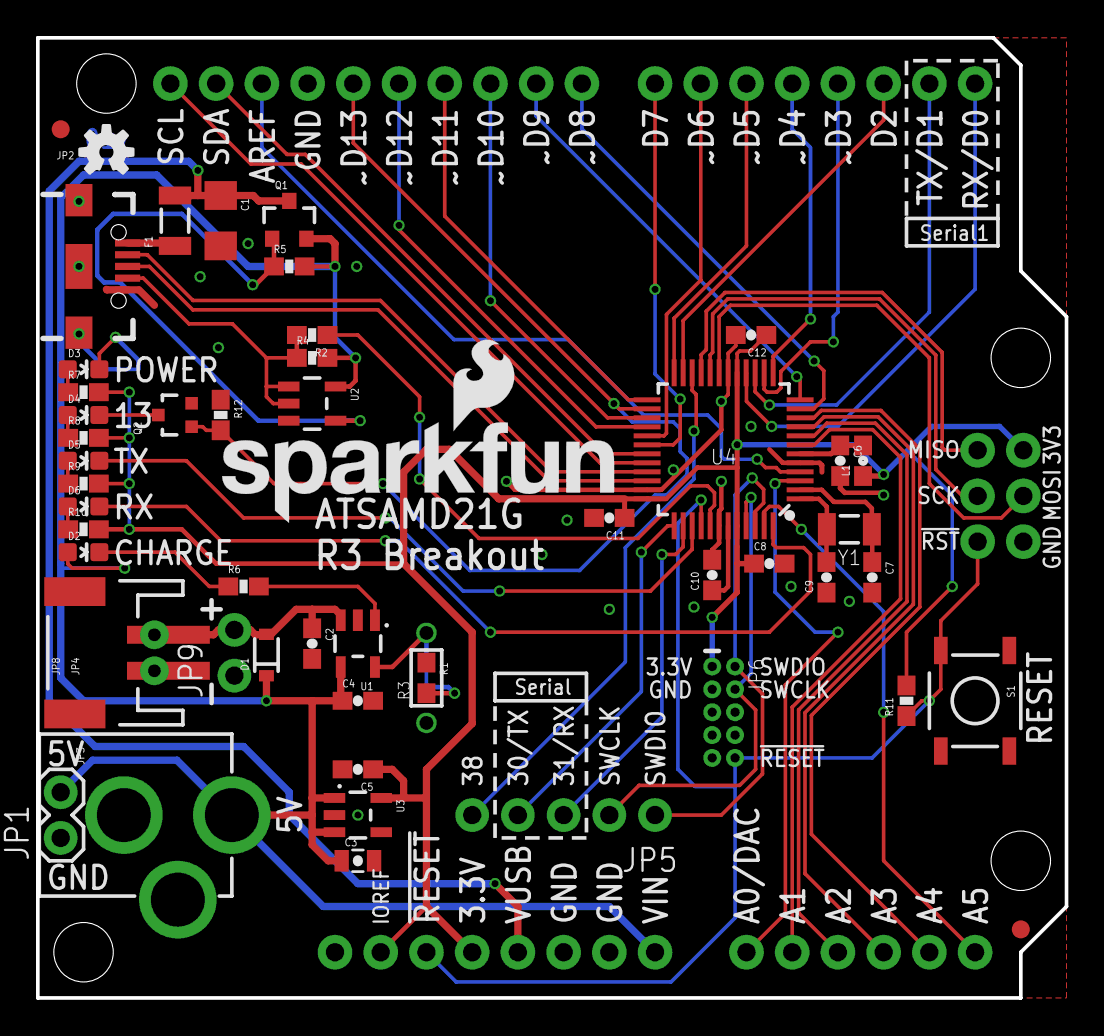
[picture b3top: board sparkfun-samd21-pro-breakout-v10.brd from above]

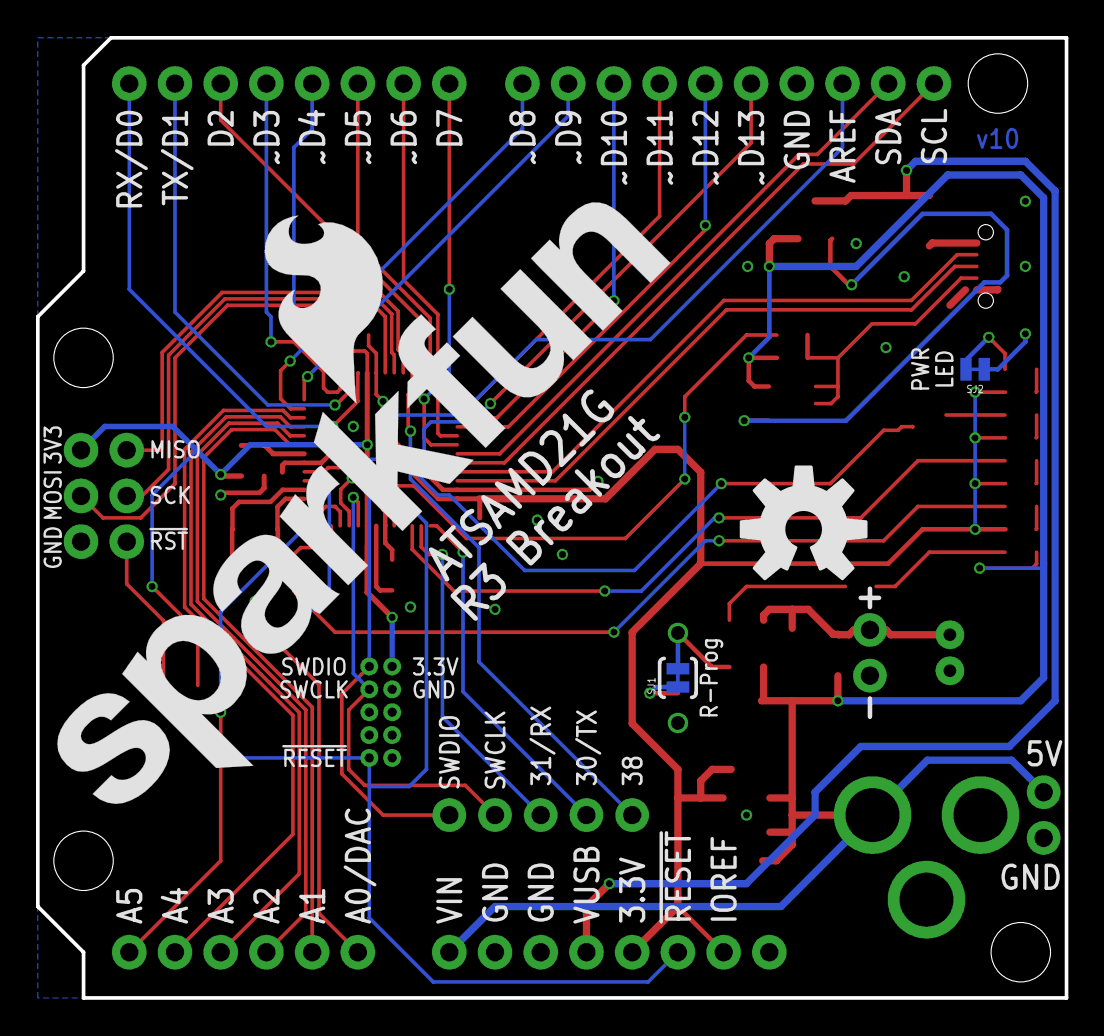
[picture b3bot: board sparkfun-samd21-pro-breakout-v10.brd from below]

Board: 2 copper layers, 57.1 x 53.3 mm, 62 parts (4 on the bottom side), 59 nets.

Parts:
C1: 2.2UF; 1206
C2, C4: 4.7uF; 0603-CAP
C3: 1.0uF; 0805-CAP
C5: 2.2uF; 0603-CAP
C6, C8, C10, C11, C12: 0.1uF; 0603-CAP
C7, C9: 15pF; 0603-CAP
D1: BAT20J; SOD-323
D2, D3: RED; LED-0603
D4: BLUE; LED-0603
D5: GREEN; LED-0603
D6: Yellow; LED-0603
F1: 500mA; PTC-1206
FID1, FID2: FIDUCIAL1X2; FIDUCIAL-1X2
FRAME1: FRAME-LEDGER; CREATIVE_COMMONS
JP1: 1X02
JP2: USB-AB-MICRO-SMD_V03
JP3: POWER_JACKPTH; POWER_JACK_PTH
JP4: JST-2-SMD
JP5: 1X05_NO_SILK
JP6: CORTEX_DEBUGPTH; 2X5-PTH-1.27MM
JP7: ARDUINO_R3NO_HOLES; ARDUINO_R3_NO_HOLES
JP8: JST-2-PTH-NS
JP9: 1X02_NO_SILK
L1: FB - 30Ohm; 0603
LOGO1: SFE_LOGO_NAME_FLAME.2_INCH; SFE_LOGO_NAME_FLAME_.2
LOGO2: SFE_LOGO_NAME_FLAME.4_INCH; SFE_LOGO_NAME_FLAME_.4
LOGO3: OSHW-LOGOS; OSHW-LOGO-S
LOGO4: OSHW-LOGOL; OSHW-LOGO-L
Q1: 2.5A/30V; SOT23-3
Q2: 2N7002PW; SOT323
R1: 3.9K; 0603
R2, R6, R7, R8, R9, R10: 330; 0603-RES
R3: PROG; 1/6W-RES
R4, R12: 100k; 0603-RES
R5: 47K; 0603-RES
R11: 10K; 0603-RES
S1: RESET; TACTILE-SWITCH-SMD
SJ1: R-prog; PAD-JUMPER-2-NC_BY_TRACE_YES_SILK
SJ2: PWR-LED; PAD-JUMPER-2-NC_BY_TRACE_NO_SILK
STANDOFF1, STANDOFF2, STANDOFF3, STANDOFF4: STAND-OFF
U1: MCP73831; SOT23-5
U2: 74AHC1G125; SOT23-5
U3: 3.3V; SOT23-5
U4: ATSAMD21G-A; TQFP-48
Y1: 32.768kHz; CRYSTAL-SMD-3.2X1.5MM

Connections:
3.3V: C5.1, C8.1, C11.1, C12.1, JP6.1, JP7.3.3V, JP7.IOREF, JP7.VCC, L1.1, R7.2, R8.2, R9.2, R10.2, R11.2, U3.5, U4.17, U4.36, U4.44
!RESET: JP6.10, JP7.RESET@1, JP7.RESET@2, R11.1, S1.3, U4.40
A0: JP7.A0, U4.3
A1: JP7.A1, U4.7
A2: JP7.A2, U4.8
A3: JP7.A3, U4.9
A4: JP7.A4, U4.10
A5: JP7.A5, U4.47
AREF: JP7.AREF, U4.4
CHG_STAT: R6.2, U1.1
D0/RXI: JP7.D0, U4.16
D1/TXO: JP7.D1, U4.15
D2: JP7.D2, U4.23
D3: JP7.D3, U4.14
D4: JP7.D4, U4.13
D5: JP7.D5, U4.24
D6: JP7.D6, U4.29
D7: JP7.D7, U4.30
D8: JP7.D8, U4.11
D9: JP7.D9, U4.12
D10: JP7.D10, U4.27
D11: JP7.D11, U4.25
D12: JP7.D12, U4.28
D13: JP7.D13, Q2.1, R12.2, U4.26
GND: C1.2, C2.2, C3.2, C4.2, C5.2, C6.2, C7.2, C8.2, C9.1, C10.2, C11.2, C12.2, JP1.1, JP2.GND1, JP2.SHIELD1, JP2.SHIELD2, JP2.SHIELD3, JP3.GND, JP3.GNDBREAK, JP4.1, JP6.3, JP6.5, JP7.GND@1, JP7.GND@2, JP7.GND@3, JP7.GND@4, JP8.1, JP9.1, Q2.2, R1.1, R3.1, R12.1, S1.1, SJ2.1, U1.2, U2.3, U3.2, U4.5, U4.18, U4.35, U4.42
unnamed: F1.1, JP2.VBUS1
unnamed: C9.2, U4.1, Y1.P$2
unnamed: D4.C, Q2.3
unnamed: C7.1, U4.2, Y1.P$1
unnamed: D3.A, R7.1
unnamed: D4.A, R8.1
unnamed: D2.C, R6.1
unnamed: D5.A, R9.1
unnamed: D6.A, R10.1
unnamed: D3.C, SJ2.2
unnamed: R1.2, SJ1.1
unnamed: R3.2, SJ1.2, U1.5
PA13: JP5.5, U4.22
PB22: JP5.4, U4.37
PB23: JP5.3, U4.38
RX_LED: D6.C, U4.48
SCL: JP7.SCL, U4.32
SDA: JP7.SDA, U4.31
SPI_MISO: JP7.MISO, U4.21
SPI_MOSI: JP7.MOSI, U4.19
SPI_SCK: JP7.SCK, U4.20
SWCLK: JP5.2, JP6.4, U4.45
SWDIO: JP5.1, JP6.2, U4.46
TX_LED: D5.C, U4.39
USB_D+: JP2.D+1, U4.34
USB_D-: JP2.D-1, U4.33
USB_HOST_EN: R2.1, U4.41
USB_HOST_POWER_EN: Q1.1, R5.1, U2.4
USB_ID: JP2.ID1, R2.2, R4.1, U2.1, U2.2
VBAT: C2.1, D1.A, JP4.2, JP8.2, JP9.2, U1.3
VDDANA: C6.1, L1.2, U4.6
VDDCORE: C10.1, U4.43
VIN: C3.1, C4.1, D1.C, D2.A, JP1.2, JP3.PWR, JP7.VIN, Q1.2, R4.2, R5.2, U1.4, U2.5, U3.1, U3.3
VUSB: C1.1, F1.2, JP7.5V, Q1.3

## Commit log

2016-05-03 Added .gitignore
2016-05-09 Added DS3231 Test Code
2016-05-10 Added SD card and RTC code to LEMSv2.ino
2016-05-26 Added files, minor changes
2016-05-27 Added pin connections, other files
2016-06-01 Added many sensors to code, datasheets
2016-06-08 Added transimpedance calculations
2016-06-10 Added parts to schematic
2016-06-21 Added library, more parts to schematic
2016-06-29 Working test of LEMSv2, soil test
2016-06-30 Added sensor stick
2016-07-03 Finished routing sensor stick
2016-07-17 Commit before converting 5TM to library
2016-07-18 Added untried 5TM test code
2016-07-20 Finished 5TM code, fixed bugs
2016-07-21 Added sleep code
2016-07-25 Changed how parts were added to BOM
2016-07-29 Determined more parts, added to lib/schematic
2016-07-31 Improved BOM and added parts
2016-08-02 Added more parts to schematic
2016-08-04 Added Li200 Test Code
2016-08-04 Added circuits to schematic
2016-08-06 Added LED circuit
2016-08-06 Added ADC and support parts
2016-08-07 Added final schematic parts
2016-08-08 Modified SD connector footprint, moved connectors
2016-08-09 Initial layout
2016-08-11 5TM library bug fix, board layout changes
2016-08-12 Fixed other 5TM checksum bug
2016-08-14 Switched 5TM power to transistor, added schottky
2016-08-15 Started routing, part changes
2016-08-16 More routing
2016-08-18 File reorganization
2016-08-18 Completed board
2016-08-21 Fixed ADS1115 problems
2016-08-24 Added gerbers and centroid files
2016-08-25 Soldermask changes and started assembly quotes
2016-08-31 Added assembly quotes and panelized gerbers
2016-09-09 Updated BOM, design finalized for assembly
2016-09-29 File reorganization, README update, Time_Set added
2016-10-02 Added Li200 Base
2016-10-06 Updated base without post
2016-10-20 Added calibration constants workbook
2016-10-24 Added modified old Li200R Base
2016-11-02 Bookkeeping
2016-11-07 Small BOM and documentation changes
2016-11-13 Added more instructions
2016-11-14 Added possible problem
2016-11-29 BOM update
2016-12-06 Wind speed changes
2016-12-06 Minor comment
2016-12-17 Minor changes and added simple matlab data viewing script
2017-01-06 Added more LEMS plotting code
2017-01-31 Added DS2 sonic anemometer test code
2017-01-31 Documentation changes
2017-05-16 Added DS2 sonic code
2017-05-18 Fixed sonic header printing bug
2017-06-02 Updated MLX housing instructions
2017-06-05 Updated code instructions
2017-06-12 Minor README changes
2017-09-06 Minor instructions changes
2017-09-29 Added LEMS scaling to BOM
2018-03-11 Updates and preparation for 2018 builds/deployments
2018-07-01 Atmos 22 code now working
2018-07-01 Refactored DS2 code
2018-07-10 Tested new DS2 code with LEMSv2 code
2018-07-15 Added initial pyrgeometer test code
2018-07-21 Minor additions to Pyrgeometer test
2018-08-25 Added pyrgeometer code to LEMS code
2018-10-01 Changed possible problems to possible improvements
2019-02-08 Added future development links to README

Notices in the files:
parts and their libraries:
SparkFun-Capacitors: Licensing: Creative Commons ShareAlike 4.0 International - https://creativecommons.org/licenses/by-sa/4.0
SparkFun-Aesthetics: Released under the Creative Commons Attribution Share-Alike 4.0 License
SparkFun-Aesthetics: https://creativecommons.org/licenses/by-sa/4.0
